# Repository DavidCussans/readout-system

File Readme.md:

SoLid readout system
====================

_Development of the readout system for the full scale SoLid experiment._

The repository is split into the separate development parts:

* sensors - The light sensors and the PCBs
* analog board - to provide bias voltage, amplify and shape the analog signals form the sensors
* digital board - to digitise the analog signals, analyse the signals in an FPGA to make trigger decisions and transmit them to a PC
* software - to collect data transmitted from the FPGA, further reduce the data and write it to disk. The interface for operators to control the system
* cabling - to connect the senors to the analog board, the analog board to the digital board, power supplies to each board, etc.
* docs - system level documents such as requirements, reports, etc.
* utility_box   design info and documentation about the utility box

Permissions
-----------

The `Readout developers` group have write access, other members of the collaboration have read access.
If you need access contact Dan Saunders.

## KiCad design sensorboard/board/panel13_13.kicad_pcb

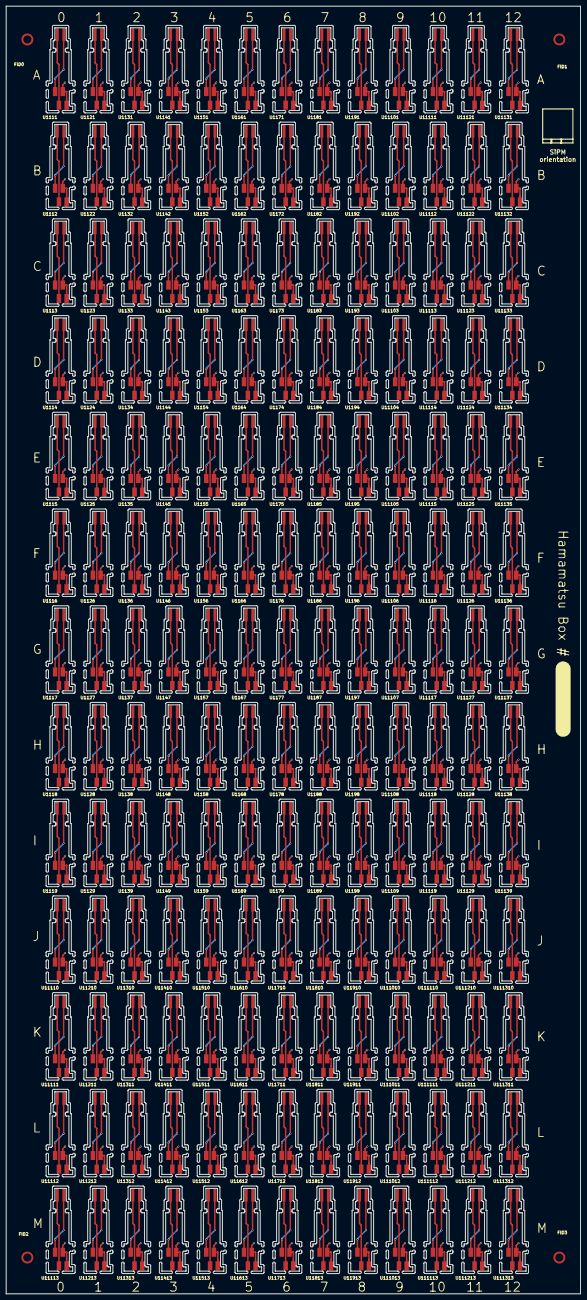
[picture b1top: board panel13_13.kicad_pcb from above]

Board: 2 copper layers, 190.0 x 426.0 mm, 173 parts (0 on the bottom side), 3 nets.

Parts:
FID0, FID1, FID2, FID3: Fiducial_Modern_CopperTop
U1111, U1112, U1113, U1114, U1115, U1116, U1117, U1118, U1119, U1121, U1122, U1123, U1124, U1125, U1126, U1127, U1128, U1129, U1131, U1132, U1133, U1134, U1135, U1136, U1137, U1138, U1139, U1141, U1142, U1143, U1144, U1145, U1146, U1147, U1148, U1149, U1151, U1152, U1153, U1154, U1155, U1156, U1157, U1158, U1159, U1161, U1162, U1163, U1164, U1165, U1166, U1167, U1168, U1169, U1171, U1172, U1173, U1174, U1175, U1176, U1177, U1178, U1179, U1181, U1182, U1183, U1184, U1185, U1186, U1187, U1188, U1189, U1191, U1192, U1193, U1194, U1195, U1196, U1197, U1198, U1199, U11101, U11102, U11103, U11104, U11105, U11106, U11107, U11108, U11109, U11110, U11111, U11111#2, U11112, U11112#2, U11113, U11113#2, U11114, U11115, U11116, U11117, U11118, U11119, U11121, U11122, U11123, U11124, U11125, U11126, U11127, U11128, U11129, U11131, U11132, U11133, U11134, U11135, U11136, U11137, U11138, U11139, U11210, U11211, U11212, U11213, U11310, U11311, U11312, U11313, U11410, U11411, U11412, U11413, U11510, U11511, U11512, U11513, U11610, U11611, U11612, U11613, U11710, U11711, U11712, U11713, U11810, U11811, U11812, U11813, U11910, U11911, U11912, U11913, U111010, U111011, U111012, U111013, U111110, U111111, U111112, U111113, U111210, U111211, U111212, U111213, U111310, U111311, U111312, U111313: SiPM_Socket; sipm_socket

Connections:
GND: U1111.1, U1111.2, U1112.1, U1112.2, U1113.1, U1113.2, U1114.1, U1114.2, U1115.1, U1115.2, U1116.1, U1116.2, U1117.1, U1117.2, U1118.1, U1118.2, U1119.1, U1119.2, U1121.1, U1121.2, U1122.1, U1122.2, U1123.1, U1123.2, U1124.1, U1124.2, U1125.1, U1125.2, U1126.1, U1126.2, U1127.1, U1127.2, U1128.1, U1128.2, U1129.1, U1129.2, U1131.1, U1131.2, U1132.1, U1132.2, U1133.1, U1133.2, U1134.1, U1134.2, U1135.1, U1135.2, U1136.1, U1136.2, U1137.1, U1137.2, U1138.1, U1138.2, U1139.1, U1139.2, U1141.1, U1141.2, U1142.1, U1142.2, U1143.1, U1143.2, U1144.1, U1144.2, U1145.1, U1145.2, U1146.1, U1146.2, U1147.1, U1147.2, U1148.1, U1148.2, U1149.1, U1149.2, U1151.1, U1151.2, U1152.1, U1152.2, U1153.1, U1153.2, U1154.1, U1154.2, U1155.1, U1155.2, U1156.1, U1156.2, U1157.1, U1157.2, U1158.1, U1158.2, U1159.1, U1159.2, U1161.1, U1161.2, U1162.1, U1162.2, U1163.1, U1163.2, U1164.1, U1164.2, U1165.1, U1165.2, U1166.1, U1166.2, U1167.1, U1167.2, U1168.1, U1168.2, U1169.1, U1169.2, U1171.1, U1171.2, U1172.1, U1172.2, U1173.1, U1173.2, U1174.1, U1174.2, U1175.1, U1175.2, U1176.1, U1176.2, U1177.1, U1177.2, U1178.1, U1178.2, U1179.1, U1179.2, U1181.1, U1181.2, U1182.1, U1182.2, U1183.1, U1183.2, U1184.1, U1184.2, U1185.1, U1185.2, U1186.1, U1186.2, U1187.1, U1187.2, U1188.1, U1188.2, U1189.1, U1189.2, U1191.1, U1191.2, U1192.1, U1192.2, U1193.1, U1193.2, U1194.1, U1194.2, U1195.1, U1195.2, U1196.1, U1196.2, U1197.1, U1197.2, U1198.1, U1198.2, U1199.1, U1199.2, U11101.1, U11101.2, U11102.1, U11102.2, U11103.1, U11103.2, U11104.1, U11104.2, U11105.1, U11105.2, U11106.1, U11106.2, U11107.1, U11107.2, U11108.1, U11108.2, U11109.1, U11109.2, U11110.1, U11110.2, U11111.1, U11111.2, U11111#2.1, U11111#2.2, U11112.1, U11112.2, U11112#2.1, U11112#2.2, U11113.1, U11113.2, U11113#2.1, U11113#2.2, U11114.1, U11114.2, U11115.1, U11115.2, U11116.1, U11116.2, U11117.1, U11117.2, U11118.1, U11118.2, U11119.1, U11119.2, U11121.1, U11121.2, U11122.1, U11122.2, U11123.1, U11123.2, U11124.1, U11124.2, U11125.1, U11125.2, U11126.1, U11126.2, U11127.1, U11127.2, U11128.1, U11128.2, U11129.1, U11129.2, U11131.1, U11131.2, U11132.1, U11132.2, U11133.1, U11133.2, U11134.1, U11134.2, U11135.1, U11135.2, U11136.1, U11136.2, U11137.1, U11137.2, U11138.1, U11138.2, U11139.1, U11139.2, U11210.1, U11210.2, U11211.1, U11211.2, U11212.1, U11212.2, U11213.1, U11213.2, U11310.1, U11310.2, U11311.1, U11311.2, U11312.1, U11312.2, U11313.1, U11313.2, U11410.1, U11410.2, U11411.1, U11411.2, U11412.1, U11412.2, U11413.1, U11413.2, U11510.1, U11510.2, U11511.1, U11511.2, U11512.1, U11512.2, U11513.1, U11513.2, U11610.1, U11610.2, U11611.1, U11611.2, U11612.1, U11612.2, U11613.1, U11613.2, U11710.1, U11710.2, U11711.1, U11711.2, U11712.1, U11712.2, U11713.1, U11713.2, U11810.1, U11810.2, U11811.1, U11811.2, U11812.1, U11812.2, U11813.1, U11813.2, U11910.1, U11910.2, U11911.1, U11911.2, U11912.1, U11912.2, U11913.1, U11913.2, U111010.1, U111010.2, U111011.1, U111011.2, U111012.1, U111012.2, U111013.1, U111013.2, U111110.1, U111110.2, U111111.1, U111111.2, U111112.1, U111112.2, U111113.1, U111113.2, U111210.1, U111210.2, U111211.1, U111211.2, U111212.1, U111212.2, U111213.1, U111213.2, U111310.1, U111310.2, U111311.1, U111311.2, U111312.1, U111312.2, U111313.1, U111313.2
unnamed: U1111.3, U1111.6, U1112.3, U1112.6, U1113.3, U1113.6, U1114.3, U1114.6, U1115.3, U1115.6, U1116.3, U1116.6, U1117.3, U1117.6, U1118.3, U1118.6, U1119.3, U1119.6, U1121.3, U1121.6, U1122.3, U1122.6, U1123.3, U1123.6, U1124.3, U1124.6, U1125.3, U1125.6, U1126.3, U1126.6, U1127.3, U1127.6, U1128.3, U1128.6, U1129.3, U1129.6, U1131.3, U1131.6, U1132.3, U1132.6, U1133.3, U1133.6, U1134.3, U1134.6, U1135.3, U1135.6, U1136.3, U1136.6, U1137.3, U1137.6, U1138.3, U1138.6, U1139.3, U1139.6, U1141.3, U1141.6, U1142.3, U1142.6, U1143.3, U1143.6, U1144.3, U1144.6, U1145.3, U1145.6, U1146.3, U1146.6, U1147.3, U1147.6, U1148.3, U1148.6, U1149.3, U1149.6, U1151.3, U1151.6, U1152.3, U1152.6, U1153.3, U1153.6, U1154.3, U1154.6, U1155.3, U1155.6, U1156.3, U1156.6, U1157.3, U1157.6, U1158.3, U1158.6, U1159.3, U1159.6, U1161.3, U1161.6, U1162.3, U1162.6, U1163.3, U1163.6, U1164.3, U1164.6, U1165.3, U1165.6, U1166.3, U1166.6, U1167.3, U1167.6, U1168.3, U1168.6, U1169.3, U1169.6, U1171.3, U1171.6, U1172.3, U1172.6, U1173.3, U1173.6, U1174.3, U1174.6, U1175.3, U1175.6, U1176.3, U1176.6, U1177.3, U1177.6, U1178.3, U1178.6, U1179.3, U1179.6, U1181.3, U1181.6, U1182.3, U1182.6, U1183.3, U1183.6, U1184.3, U1184.6, U1185.3, U1185.6, U1186.3, U1186.6, U1187.3, U1187.6, U1188.3, U1188.6, U1189.3, U1189.6, U1191.3, U1191.6, U1192.3, U1192.6, U1193.3, U1193.6, U1194.3, U1194.6, U1195.3, U1195.6, U1196.3, U1196.6, U1197.3, U1197.6, U1198.3, U1198.6, U1199.3, U1199.6, U11101.3, U11101.6, U11102.3, U11102.6, U11103.3, U11103.6, U11104.3, U11104.6, U11105.3, U11105.6, U11106.3, U11106.6, U11107.3, U11107.6, U11108.3, U11108.6, U11109.3, U11109.6, U11110.3, U11110.6, U11111.3, U11111.6, U11111#2.3, U11111#2.6, U11112.3, U11112.6, U11112#2.3, U11112#2.6, U11113.3, U11113.6, U11113#2.3, U11113#2.6, U11114.3, U11114.6, U11115.3, U11115.6, U11116.3, U11116.6, U11117.3, U11117.6, U11118.3, U11118.6, U11119.3, U11119.6, U11121.3, U11121.6, U11122.3, U11122.6, U11123.3, U11123.6, U11124.3, U11124.6, U11125.3, U11125.6, U11126.3, U11126.6, U11127.3, U11127.6, U11128.3, U11128.6, U11129.3, U11129.6, U11131.3, U11131.6, U11132.3, U11132.6, U11133.3, U11133.6, U11134.3, U11134.6, U11135.3, U11135.6, U11136.3, U11136.6, U11137.3, U11137.6, U11138.3, U11138.6, U11139.3, U11139.6, U11210.3, U11210.6, U11211.3, U11211.6, U11212.3, U11212.6, U11213.3, U11213.6, U11310.3, U11310.6, U11311.3, U11311.6, U11312.3, U11312.6, U11313.3, U11313.6, U11410.3, U11410.6, U11411.3, U11411.6, U11412.3, U11412.6, U11413.3, U11413.6, U11510.3, U11510.6, U11511.3, U11511.6, U11512.3, U11512.6, U11513.3, U11513.6, U11610.3, U11610.6, U11611.3, U11611.6, U11612.3, U11612.6, U11613.3, U11613.6, U11710.3, U11710.6, U11711.3, U11711.6, U11712.3, U11712.6, U11713.3, U11713.6, U11810.3, U11810.6, U11811.3, U11811.6, U11812.3, U11812.6, U11813.3, U11813.6, U11910.3, U11910.6, U11911.3, U11911.6, U11912.3, U11912.6, U11913.3, U11913.6, U111010.3, U111010.6, U111011.3, U111011.6, U111012.3, U111012.6, U111013.3, U111013.6, U111110.3, U111110.6, U111111.3, U111111.6, U111112.3, U111112.6, U111113.3, U111113.6, U111210.3, U111210.6, U111211.3, U111211.6, U111212.3, U111212.6, U111213.3, U111213.6, U111310.3, U111310.6, U111311.3, U111311.6, U111312.3, U111312.6, U111313.3, U111313.6
unnamed: U1111.4, U1111.5, U1112.4, U1112.5, U1113.4, U1113.5, U1114.4, U1114.5, U1115.4, U1115.5, U1116.4, U1116.5, U1117.4, U1117.5, U1118.4, U1118.5, U1119.4, U1119.5, U1121.4, U1121.5, U1122.4, U1122.5, U1123.4, U1123.5, U1124.4, U1124.5, U1125.4, U1125.5, U1126.4, U1126.5, U1127.4, U1127.5, U1128.4, U1128.5, U1129.4, U1129.5, U1131.4, U1131.5, U1132.4, U1132.5, U1133.4, U1133.5, U1134.4, U1134.5, U1135.4, U1135.5, U1136.4, U1136.5, U1137.4, U1137.5, U1138.4, U1138.5, U1139.4, U1139.5, U1141.4, U1141.5, U1142.4, U1142.5, U1143.4, U1143.5, U1144.4, U1144.5, U1145.4, U1145.5, U1146.4, U1146.5, U1147.4, U1147.5, U1148.4, U1148.5, U1149.4, U1149.5, U1151.4, U1151.5, U1152.4, U1152.5, U1153.4, U1153.5, U1154.4, U1154.5, U1155.4, U1155.5, U1156.4, U1156.5, U1157.4, U1157.5, U1158.4, U1158.5, U1159.4, U1159.5, U1161.4, U1161.5, U1162.4, U1162.5, U1163.4, U1163.5, U1164.4, U1164.5, U1165.4, U1165.5, U1166.4, U1166.5, U1167.4, U1167.5, U1168.4, U1168.5, U1169.4, U1169.5, U1171.4, U1171.5, U1172.4, U1172.5, U1173.4, U1173.5, U1174.4, U1174.5, U1175.4, U1175.5, U1176.4, U1176.5, U1177.4, U1177.5, U1178.4, U1178.5, U1179.4, U1179.5, U1181.4, U1181.5, U1182.4, U1182.5, U1183.4, U1183.5, U1184.4, U1184.5, U1185.4, U1185.5, U1186.4, U1186.5, U1187.4, U1187.5, U1188.4, U1188.5, U1189.4, U1189.5, U1191.4, U1191.5, U1192.4, U1192.5, U1193.4, U1193.5, U1194.4, U1194.5, U1195.4, U1195.5, U1196.4, U1196.5, U1197.4, U1197.5, U1198.4, U1198.5, U1199.4, U1199.5, U11101.4, U11101.5, U11102.4, U11102.5, U11103.4, U11103.5, U11104.4, U11104.5, U11105.4, U11105.5, U11106.4, U11106.5, U11107.4, U11107.5, U11108.4, U11108.5, U11109.4, U11109.5, U11110.4, U11110.5, U11111.4, U11111.5, U11111#2.4, U11111#2.5, U11112.4, U11112.5, U11112#2.4, U11112#2.5, U11113.4, U11113.5, U11113#2.4, U11113#2.5, U11114.4, U11114.5, U11115.4, U11115.5, U11116.4, U11116.5, U11117.4, U11117.5, U11118.4, U11118.5, U11119.4, U11119.5, U11121.4, U11121.5, U11122.4, U11122.5, U11123.4, U11123.5, U11124.4, U11124.5, U11125.4, U11125.5, U11126.4, U11126.5, U11127.4, U11127.5, U11128.4, U11128.5, U11129.4, U11129.5, U11131.4, U11131.5, U11132.4, U11132.5, U11133.4, U11133.5, U11134.4, U11134.5, U11135.4, U11135.5, U11136.4, U11136.5, U11137.4, U11137.5, U11138.4, U11138.5, U11139.4, U11139.5, U11210.4, U11210.5, U11211.4, U11211.5, U11212.4, U11212.5, U11213.4, U11213.5, U11310.4, U11310.5, U11311.4, U11311.5, U11312.4, U11312.5, U11313.4, U11313.5, U11410.4, U11410.5, U11411.4, U11411.5, U11412.4, U11412.5, U11413.4, U11413.5, U11510.4, U11510.5, U11511.4, U11511.5, U11512.4, U11512.5, U11513.4, U11513.5, U11610.4, U11610.5, U11611.4, U11611.5, U11612.4, U11612.5, U11613.4, U11613.5, U11710.4, U11710.5, U11711.4, U11711.5, U11712.4, U11712.5, U11713.4, U11713.5, U11810.4, U11810.5, U11811.4, U11811.5, U11812.4, U11812.5, U11813.4, U11813.5, U11910.4, U11910.5, U11911.4, U11911.5, U11912.4, U11912.5, U11913.4, U11913.5, U111010.4, U111010.5, U111011.4, U111011.5, U111012.4, U111012.5, U111013.4, U111013.5, U111110.4, U111110.5, U111111.4, U111111.5, U111112.4, U111112.5, U111113.4, U111113.5, U111210.4, U111210.5, U111211.4, U111211.5, U111212.4, U111212.5, U111213.4, U111213.5, U111310.4, U111310.5, U111311.4, U111311.5, U111312.4, U111312.5, U111313.4, U111313.5

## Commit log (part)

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2015-04-01 Start writing requirements document.
2015-04-01 Added a version number to requirements.
2015-04-01 Fixed some indentation.
2015-04-01 No abstract in requirements.
2015-04-01 Playing with geometry
2015-04-08 Added dead time requirement.
2015-05-21 Initial repository structure.
2015-05-27 Estimates of signal rates.
2015-05-29 First draft of 18/19th meeting summary.
2015-06-01 Added a paragraph on modularity and layout.
2015-07-08 Made directory for analog board simulations.
2015-07-09 Adding simulation files and Latex source file
2015-08-24 Code for programming LMP9007 SPI registers.
2015-08-24 Initial library for controlling ADC (See issue #13)
2015-09-01 Initial ADC testing code (see issue #13)
2015-09-04 Close to test for ADC communication (see issue #13).
2015-09-15 beta version of the schematic 8 channels , board : analogue part execept the bias is done.
2015-09-18 pre production PCB version
2015-09-18 PCB ready for production
2015-09-24 bug feed back
2015-10-04 added remarks and picture
2015-10-16 itemize->enumerate in reqs.
2016-01-05 added MPPC PCB proposal
2016-01-14 Addedd wishbone I2C class.
2016-01-15 Test for I2C bus and more debugging.
2016-01-18 Added some instructions to testi2c.py
2016-01-18 Bug fix in I2CCore.write()
2016-01-19 Actually return data from I2CCore.read()
2016-01-22 Parse SiLab's clock configuration text file (see issue #18)
2016-01-27 added dark count study
2016-01-27 Added some images related to cabling plans.
2016-02-01 Some diagrams of software plan.
2016-02-02 Some images for digital test status
2016-02-02 Some photos of digital boards.
2016-02-03 Si5326 configuration updated to newest design
2016-02-05 Talk to ADC via SPI --> only 0s read back (to be solved)
2016-02-07 ADC configuration works!
2016-02-08 Diagram of mechanics mounting idea.
2016-02-09 added ground spring for analogue compartment
2016-02-10 added power supply considerations
2016-02-15 put address spi/i2c into io
2016-02-16 added the operation instructions for the analogue board
2016-02-17 ADC and Clock chip configuration + address tables
2016-02-17 Starting to clean up FPGA controlling code.
2016-02-18 Made area for power supply documents.
2016-02-19 Added simple library to control bias via uC board.
2016-02-22 moved cabling/power supply related info to power supply dir
2016-02-22 Added David C's code for environmental chamber.
2016-02-23 Remove top two bits of samples when storing data.
2016-02-23 Allow sipmcalibrationrun.py to use trim voltages, use timestamp in filename.
2016-02-23 Tested I2C control of bias DACs.
2016-02-23 Read current temp before waiting.
2016-02-23 Store trim voltage in output when taking data.
2016-02-25 Tweaked fitspa ranges.
2016-02-26 Updated Dave's talk_grab.py for new register names.
2016-02-26 Easy script to run multiple SiPM calibration runs at a single temperature.
2016-02-26 Controlling ADC via SPICore class.
2016-02-29 added the pdf file
2016-02-29 removed *.pdf from .gitignore
2016-02-29 redo the simulation with the amplifier solution. propsoe this to be implemented
2016-03-03 Documenting code.
2016-03-03 Count saved waveforms.
2016-03-15 Removed use of biasboard.py
2016-03-15 Simple program to set bias DAC voltages for testing.
2016-03-15 Reconfigure clock chip if it doesn't have lock.
2016-03-15 Add a flag for asserting a minimum firmware version.
2016-03-16 Bug fixes.
2016-03-18 Images for electronics spec.
2016-03-24 Fixed bug in checking minimum firmware version.
2016-04-20 temp 32 a board sch
2016-04-21 analogue board design status 21 April
2016-04-21 Annotated schematic for pins using CPLD.
2016-04-26 dc patch docs
2016-04-27 higher V5 and doc / production correctiions
2016-05-03 corrected offset , interchange vout+ ,vout- offset
2016-05-03 updated instructions for vout+ vout - change
2016-05-19 added MPPC board connection verificatoin doc
2016-05-20 new dir for original prototype design files
2016-05-30 add sub dirs for differnt versions of the analogue brd's
2016-06-01 added pdf file
2016-06-07 Firs candidate for v1.0 electronics spec.
2016-06-09 Added missing gimage for electronics spec.
2016-06-09 added power supply candidates and I2C interface card info
2016-06-13 Allow bias = 0 V
2016-06-13 New 7 x 13 double sided SiPM PCB panel.
2016-06-14 added design doc's calcs
2016-06-14 updated design info I2C interface brd
2016-06-15 Cleaning up repo for old 13x7 panel.
2016-06-17 updated schematics I2c interface other info added
2016-06-17 added zener to the alert line
2016-06-22 Left a space between rows, bigger fiducials, larger tabs.
2016-06-24 MPPC first batch data Hamamatsu
2016-06-27 added per tray serial nr sheet and pictures
2016-06-28 Lowered Vdd a little on global and trim DACs based on measurement.
2016-06-28 Allow voltage scans and setting voltage with trims.
2016-06-30 Drawings of planned channel routing for Gent 8x8 plane.
2016-06-30 Updated analog to digital channel numbering, see issue #50.
2016-06-30 Updated based on Wim's comments. See issue #42.
2016-07-04 review analogue board schematics
2016-07-05 Analysis scripts updated.
2016-07-05 Code to analyze the output of the 8 channel test setup
2016-07-05 removed root file on Nicks request, added instructions to create it
2016-07-14 SiPm cable info, test results brd 3
2016-07-18 V1 electronics spec.
2016-07-22 added data sheets and change info , calculations
2016-07-27 cmm test repeated
2016-07-27 Added a -u / --notemp option to allow use of script without environmental chamber
2016-07-28 Script to check the accuracy of the high voltage setting
2016-07-28 Option to only read current DAC voltages.
2016-07-28 Voltage scans requested by Simon. See issue #55.
2016-08-03 moved baseline storage from root to txt file, included txt file
2016-08-03 created and added Makefile
2016-08-09 Pin mapping for inside the enclosure.
2016-08-23 just some extra sim circuit
2016-08-30 correction in dimension board
2016-09-01 Initial support for Gent boards.
    Frontend takes board name parameter to pick from connection list.
    Currently supported by setvoltages.py
2016-09-01 Named FGPAs for Gent test plane.
2016-09-02 Linking Birstol stuff to Gent.
2016-09-02 Correct IP addresses for Gent boards.
2016-09-05 Tidying up some things.
2016-09-05 Untested programme to monitor temperature of test plane.
2016-09-05 Channel mapping includes Gent.
2016-09-05 Plot multiple waveforms.
2016-09-05 Log temperature from probes in test plane.
2016-09-06 Fixed inconsistency betweeh histo and waveform chan mapping.
2016-09-06 Allow per-channel trim in storedata.py
2016-09-08 Add verbose option to temperature.py
2016-09-13 Basic FPGA configuration.
2016-09-14 Store list of temperatures.
2016-09-14 Multi-board support for voltage scans.
2016-09-19 Support two temperature sensors in detector.
2016-09-20 Support active command for temperature update.
    The microcontroller now polls the UART interface.
    The software must send "T" to the microcontroller,
    it will then return the temperature and date string.
2016-09-27 Dave's readout test programs.
2016-09-27 Address tables.
2016-09-28 Name Bristol boards.
2016-09-28 Sketch of noisespectrum program.
2016-09-29 Power spectrum calculation added
2016-09-30 Added the analysis part of Wouter's code with minor changes to have it compile
2016-10-04 Graphs for noise spectrum.
    Using numpy's real fft.
2016-10-04 Wait for input if plotting noise spectrum during run.
2016-10-06 added latest analogue board schematics
2016-10-13 sipmcalibration run uses board name.
2016-10-13 Pick up correct SiPMs for Bristol test stand.
2016-10-18 Fixed bug in online noise spectrum.
    The online noise spectrum was getting messed up by including the
    non sample bits, fixed by bitwise and with 0x3fff.
    Also allow choice of channel to plot in real time and at the
    end of the run draw a 2D histogram of the channels vs
    frequencies.
2016-10-18 updated ordering info in schematic and BOM list ( fuses , DIN 41612)
2016-10-30 Hopefully easier to cut out.
2016-10-30 Updated date on silk screen.
2016-10-30 Removed unwated labels on SiPM PCB.
2016-11-02 rermoved quotation version amplifier board added production versiont
2016-11-08 added temperature sensor and humidity sensor board concepts
2016-11-16 ref issue #64 added outline script for 64 chan i2c
2016-11-16 ref issue #64 end of day edit
2016-11-18 Fix issue #65.
    Problem was microcontroller doing temperture measurements
    not responding after a reset. It needs to be sent a message
    to start up. This should now do that each time a power cycle
    occurs. This should allow data taking as normal.
2016-11-18 re #64 8bit conversion and registry reads prototype
2016-11-21 ref issue#64 WIP pre-meeting update
2016-11-24 Adding manufacturing data and quote from EASL
2016-12-10 Initial files for the i2c mux sensor board
2016-12-21 New version of the i2c mux board
2017-01-04 Refining work after Sylvester
2017-01-12 Reformat sipmcalibrationrun name with trims.
2017-01-13 Added luminosity sensor board
2017-01-13 updated documentation after testing the PCB's for T and H sensor
2017-01-18 added info for the TSENSOR boards
2017-01-19 added analogue amplifier test board, pict T and H sensor
2017-02-07 Hamamatsu sensor information.
2017-02-10 Tests for CPLD lines.
2017-02-22 new SiPm cabling
2017-03-16 update design doc
2017-04-07 Documentation update for the 32ch amplifier board (quotation version)
2017-04-10 Adding AD8132 based circuit with open circuit instead of SiPM
2017-04-13 changed bom list for SOL_AMP3
2017-04-26 Adding manufacturing information for second version of 64-channel ADC+FPGA board ( pc051c )
    This is a copy of information held in subversion repository https://svn2.phy.bris.ac.uk/svn/uob-hep-pc051a ( will be moved to https://svn.phy.bris.ac.uk/svn/uob-hep-pc051a soon
2017-04-27 Adding manufacturing data for clock / synchronization system
    Consists of two boards:
    1) FMC which connects to FPGA carrier board pc054a_fmc-manufacturing-artwork-2017-02-07.zip
    2) Clock/fanout board pc054a_toplevel-manufacturing-artwork-2017-04-27.zip
    The Zip archives contain the PCB fabrication and assembly information
    These files are copies of the definitive design information held at https://svn2.phy.bris.ac.uk/svn/uob-hep-pc054a
    ( will soon be moved to https://svn.phy.bris.ac.uk/svn/uob-hep-pc054a )
2017-04-28 Adding manufacturing data for I2C passthrough.
2017-04-28 Adding manufacturing information for power filter board
2017-05-05 Updated artwork for power filter board.
2017-05-05 Removing out of date power filter artwork
2017-05-09 added version 2.0 production info amplifier board
2017-05-14 Updated artwork with final versions for manufacture
2017-05-16 removed production version 2.1 , added production version 2.2
2017-05-25 Adding Readme file , PCB database files ( Cadence Allegro format ) and assembly drawings for SoLiD clock board and interface FMC
2017-05-25 Updating Readme.md
2017-05-30 Adding Cadence Allegro PCB database information for ADC+FPGA board (pc051c)
2017-06-20 Named batches on Hamamatsu data.
2017-06-29 Moved ictest to readout-system
2017-06-29 Move ADC timing test to readout-system
2017-06-30 Test seeing SiPM pulses.
2017-07-06 Adding simple description of components in readout syste,
2017-07-25 Adding figure of pc051a with link positions for power
2017-08-28 added data sheets for analogue board after disk change
2017-08-31 iAdding schematic for 64 chan prototype board
2017-08-31 ignore viewer files
2017-08-31 added data sheets for ADC board components
2017-09-15 Readme.md edited online with Bitbucket
2017-10-06 Readme.md created online with Bitbucket
2017-10-16 Adding CAD files for JTAG board in Eagle format.
2017-10-17 Edited Readme.md
2017-10-18 added JTAG info
2017-10-20 Comitting schematic for production boards ( Change w.r.t. 12may17 is to move two LEDs from FPGA to CPLD ( FPGA pins moved to SFP_LOS ) )
2017-10-23 Adding information about how to patch clock board power supply.
2017-10-30 Adding CAD files and parts list for service boxes.
2017-11-03 * Adding Mechanical CAD files for services box. * Adding PCB design CAD files for main power PCB ( Design Spark format )
2017-11-28 added minnow brd hw info
2018-07-25 Adding manufacturing information and schematics for 8 channel board ( for completeness ).
2019-02-26 added utility box info , more data sheets and removed empty .ignore files
